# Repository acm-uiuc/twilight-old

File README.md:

# Twilight

## Usage

    pip install -r requirements.txt
    FLASK_APP=twilight.py flask run
    
## POSTing

    curl -H "token: foo" -X post http://localhost:5000 -d '{"abc":1}'

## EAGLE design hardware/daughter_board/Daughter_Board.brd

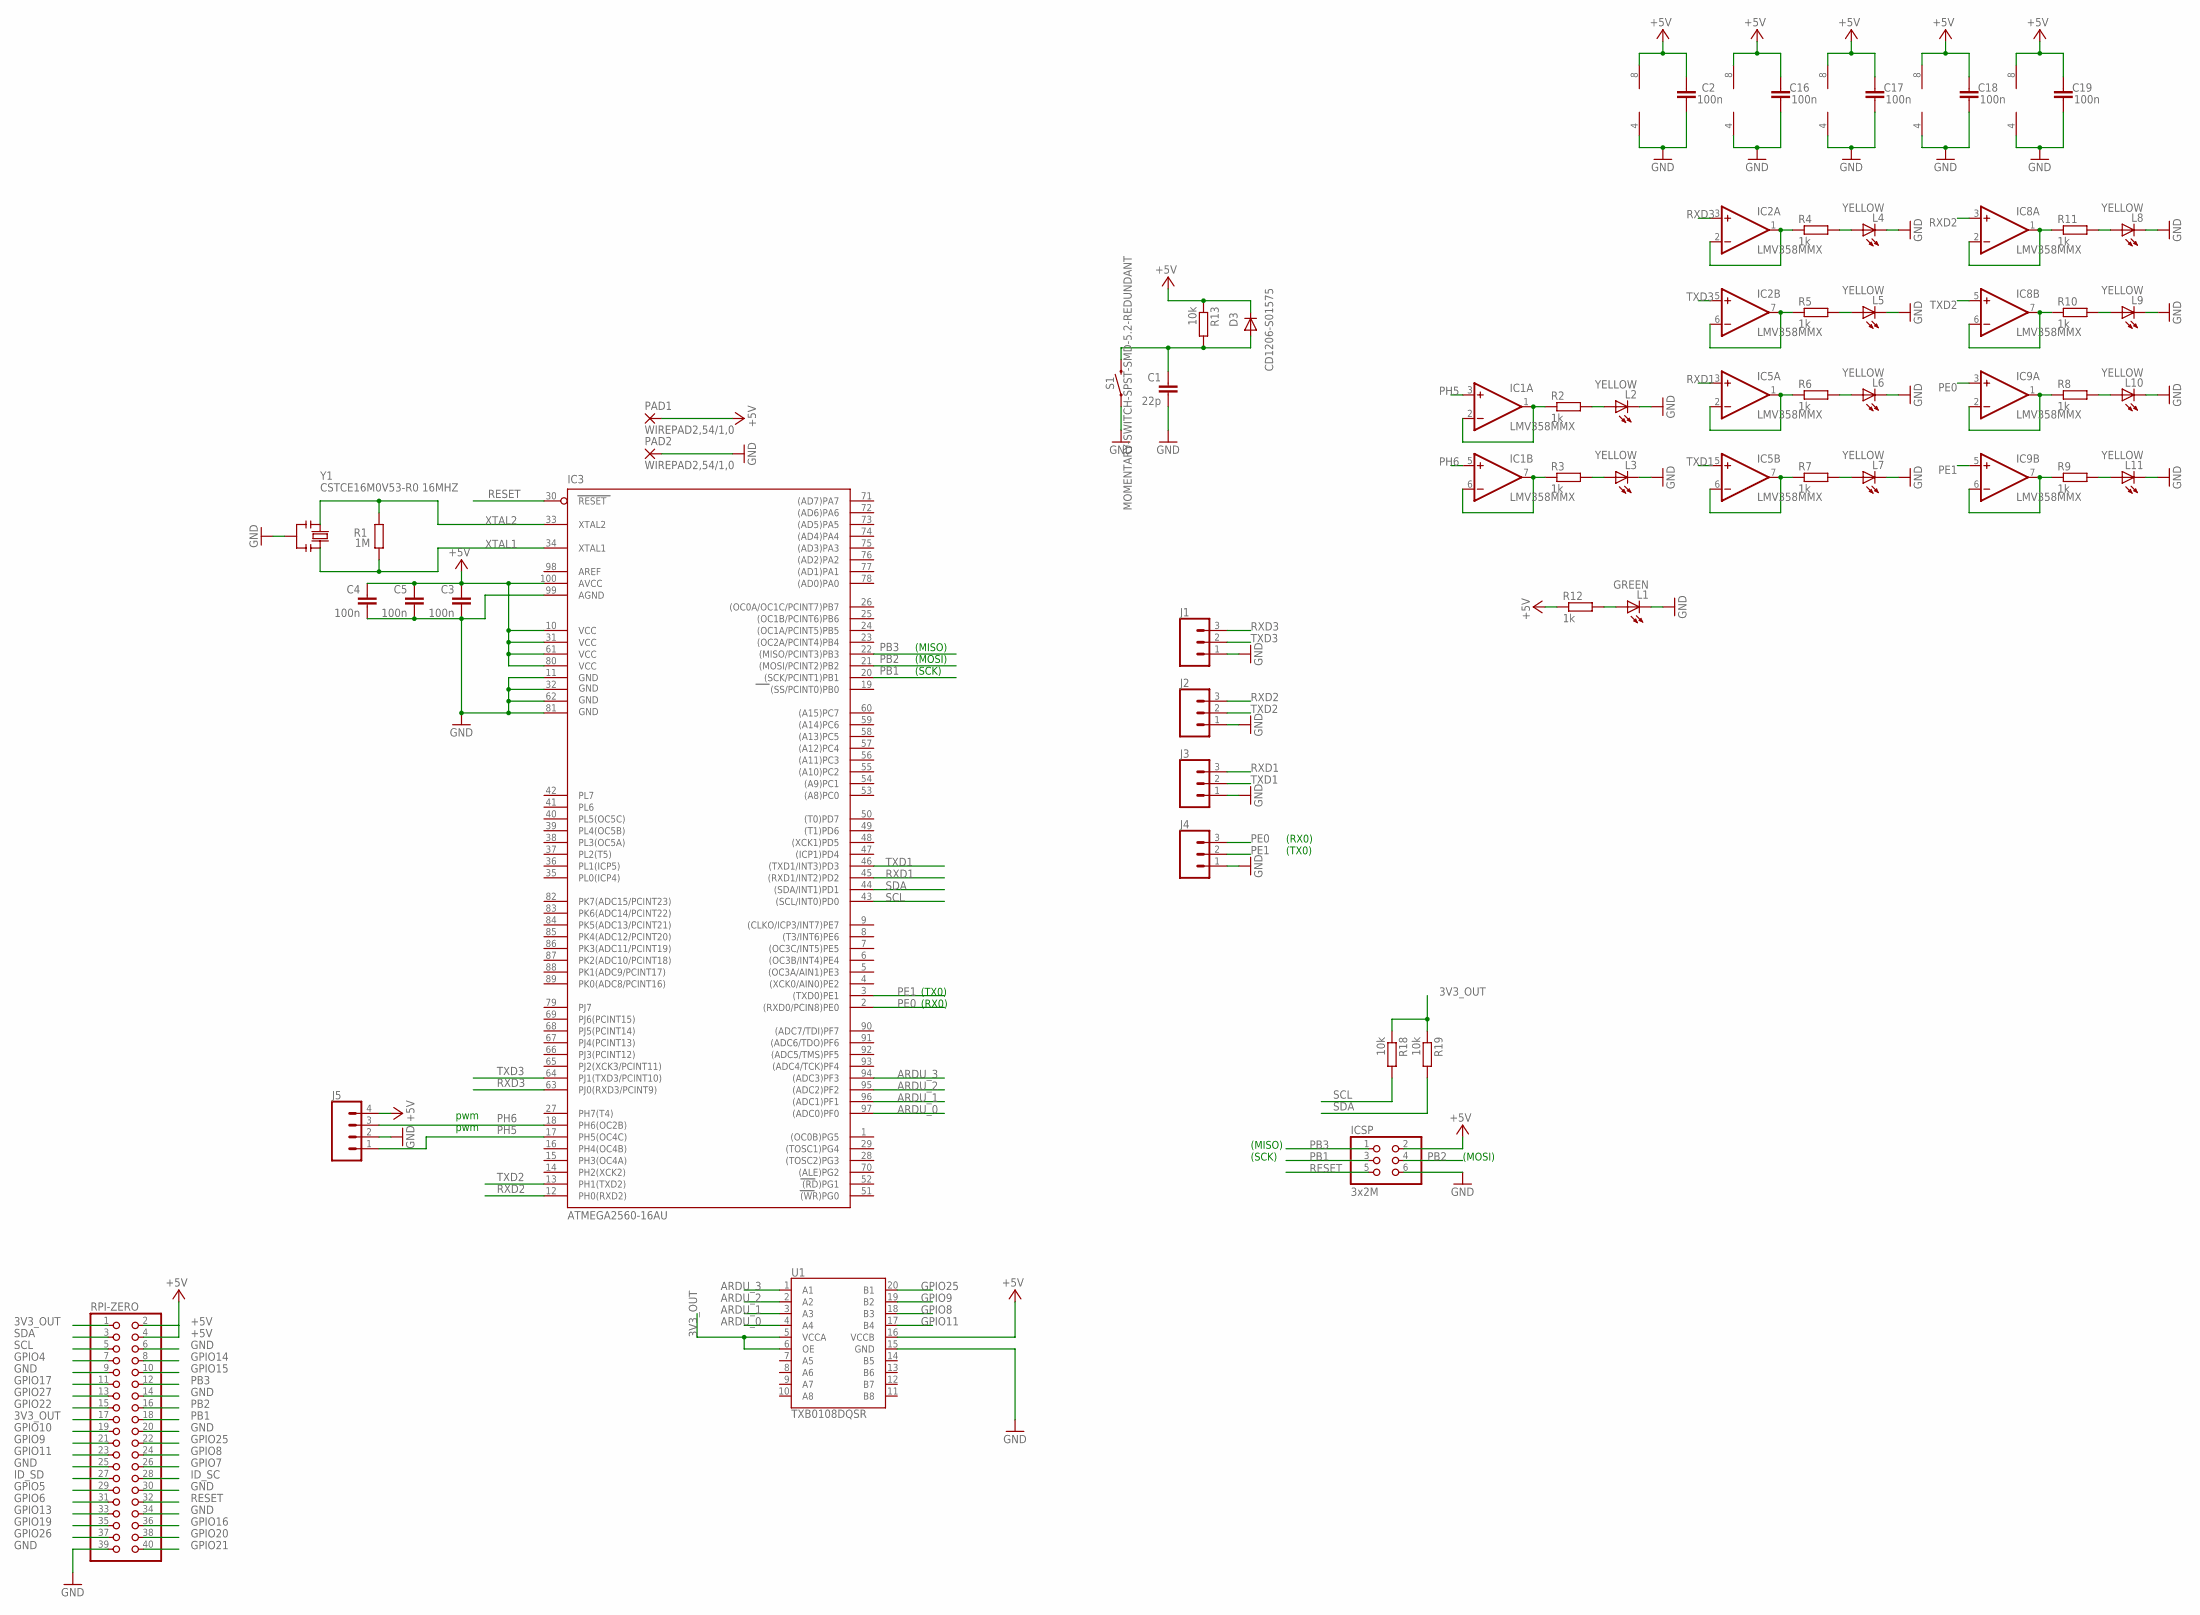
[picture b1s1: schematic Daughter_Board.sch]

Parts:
C1: 22p; C0603-ROUND
C2, C3, C4, C5, C16, C17, C18, C19: 100n; C0603-ROUND
D3: CD1206-S01575; MINIMELF
IC1, IC2, IC5, IC8, IC9: LMV358MMX; MSOP08
IC3: ATMEGA2560-16AU; TQFP100
ICSP: 3x2M; 2X03
J1, J2, J3, J4: CONN_03; 1X03
J5: CONN_04; 1X04
L1: GREEN; CHIP-LED0805
L2, L3, L4, L5, L6, L7, L8, L9, L10, L11: YELLOW; CHIP-LED0805
PAD1, PAD2: WIREPAD2,54/1,0; 2,54/1,0
R1: 1M; R0603-ROUND
R2, R3, R4, R5, R6, R7, R8, R9, R10, R11, R12: 1k; R0603
R13, R18, R19: 10k; R0603
RPI-ZERO: PINHD-2X20; 2X20
S1: MOMENTARY-SWITCH-SPST-SMD-5.2-REDUNDANT; TACTILE_SWITCH_SMD_5.2MM
U1: TXB0108DQSR; UFDFN-20
Y1: CSTCE16M0V53-R0 16MHZ; RESONATOR

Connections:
3V3_OUT: R18.1, R19.1, RPI-ZERO.1, RPI-ZERO.17, U1.5 (VCCA), U1.6 (OE)
+5V: C2.2, C3.1, C4.1, C5.1, C16.2, C17.2, C18.2, C19.2, D3.C, IC1.8 (V+), IC2.8 (V+), IC3.10 (VCC), IC3.31 (VCC1), IC3.61 (VCC2), IC3.80 (VCC3), IC3.100 (AVCC), IC5.8 (V+), IC8.8 (V+), IC9.8 (V+), ICSP.2, J5.4, PAD1.1, R12.1, R13.1, RPI-ZERO.2, RPI-ZERO.4, U1.16 (VCCB)
ARDU_0: IC3.97 ((ADC0)PF0), U1.4 (A4)
ARDU_1: IC3.96 ((ADC1)PF1), U1.3 (A3)
ARDU_2: IC3.95 ((ADC2)PF2), U1.2 (A2)
ARDU_3: IC3.94 ((ADC3)PF3), U1.1 (A1)
GND: C1.2, C2.1, C3.2, C4.2, C5.2, C16.1, C17.1, C18.1, C19.1, IC1.4 (V-), IC2.4 (V-), IC3.11 (GND), IC3.32 (GND1), IC3.62 (GND2), IC3.81 (GND3), IC3.99 (AGND), IC5.4 (V-), IC8.4 (V-), IC9.4 (V-), ICSP.6, J1.1, J2.1, J3.1, J4.1, J5.2, L1.C, L2.C, L3.C, L4.C, L5.C, L6.C, L7.C, L8.C, L9.C, L10.C, L11.C, PAD2.1, RPI-ZERO.6, RPI-ZERO.9, RPI-ZERO.14, RPI-ZERO.20, RPI-ZERO.25, RPI-ZERO.30, RPI-ZERO.34, RPI-ZERO.39, S1.1, S1.2 (1), U1.15 (GND), Y1.2
GPIO4: RPI-ZERO.7
GPIO5: RPI-ZERO.29
GPIO6: RPI-ZERO.31
GPIO7: RPI-ZERO.26
GPIO8: RPI-ZERO.24, U1.18 (B3)
GPIO9: RPI-ZERO.21, U1.19 (B2)
GPIO10: RPI-ZERO.19
GPIO11: RPI-ZERO.23, U1.17 (B4)
GPIO13: RPI-ZERO.33
GPIO14: RPI-ZERO.8
GPIO15: RPI-ZERO.10
GPIO16: RPI-ZERO.36
GPIO17: RPI-ZERO.11
GPIO19: RPI-ZERO.35
GPIO20: RPI-ZERO.38
GPIO21: RPI-ZERO.40
GPIO22: RPI-ZERO.15
GPIO25: RPI-ZERO.22, U1.20 (B1)
GPIO26: RPI-ZERO.37
GPIO27: RPI-ZERO.13
ID_SC: RPI-ZERO.28
ID_SD: RPI-ZERO.27
unnamed: L3.A, R3.2
unnamed: L2.A, R2.2
unnamed: L1.A, R12.2
unnamed: IC1.1 (OUT), IC1.2 (-IN), R2.1
unnamed: IC5.6 (-IN), IC5.7 (OUT), R7.1
unnamed: IC1.6 (-IN), IC1.7 (OUT), R3.1
unnamed: IC5.1 (OUT), IC5.2 (-IN), R6.1
unnamed: IC2.6 (-IN), IC2.7 (OUT), R5.1
unnamed: IC2.1 (OUT), IC2.2 (-IN), R4.1
unnamed: L4.A, R4.2
unnamed: L5.A, R5.2
unnamed: IC8.1 (OUT), IC8.2 (-IN), R11.1
unnamed: L7.A, R7.2
unnamed: L6.A, R6.2
unnamed: IC8.6 (-IN), IC8.7 (OUT), R10.1
unnamed: IC9.1 (OUT), IC9.2 (-IN), R8.1
unnamed: IC9.6 (-IN), IC9.7 (OUT), R9.1
unnamed: L11.A, R9.2
unnamed: L10.A, R8.2
unnamed: L8.A, R11.2
unnamed: L9.A, R10.2
PB1: IC3.20 ((SCK/PCINT1)PB1), ICSP.3, RPI-ZERO.18
PB2: IC3.21 ((MOSI/PCINT2)PB2), ICSP.4, RPI-ZERO.16
PB3: IC3.22 ((MISO/PCINT3)PB3), ICSP.1, RPI-ZERO.12
PE0: IC3.2 ((RXD0/PCIN8)PE0), IC9.3 (+IN), J4.3
PE1: IC3.3 ((TXD0)PE1), IC9.5 (+IN), J4.2
PH5: IC1.3 (+IN), IC3.17 (PH5(OC4C)), J5.1
PH6: IC1.5 (+IN), IC3.18 (PH6(OC2B)), J5.3
RESET: C1.1, D3.A, IC3.30 (RESET), ICSP.5, R13.2, RPI-ZERO.32, S1.3 (2), S1.4 (2)
RXD1: IC3.45 ((RXD1/INT2)PD2), IC5.3 (+IN), J3.3
RXD2: IC3.12 (PH0(RXD2)), IC8.3 (+IN), J2.3
RXD3: IC2.3 (+IN), IC3.63 (PJ0(RXD3/PCINT9)), J1.3
SCL: IC3.43 ((SCL/INT0)PD0), R18.2, RPI-ZERO.5
SDA: IC3.44 ((SDA/INT1)PD1), R19.2, RPI-ZERO.3
TXD1: IC3.46 ((TXD1/INT3)PD3), IC5.5 (+IN), J3.2
TXD2: IC3.13 (PH1(TXD2)), IC8.5 (+IN), J2.2
TXD3: IC2.5 (+IN), IC3.64 (PJ1(TXD3/PCINT10)), J1.2
XTAL1: IC3.34 (XTAL1), R1.1, Y1.3
XTAL2: IC3.33 (XTAL2), R1.2, Y1.1

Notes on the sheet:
pwm
(TX0)
(RX0)
(MISO)
(SCK)
(MOSI)

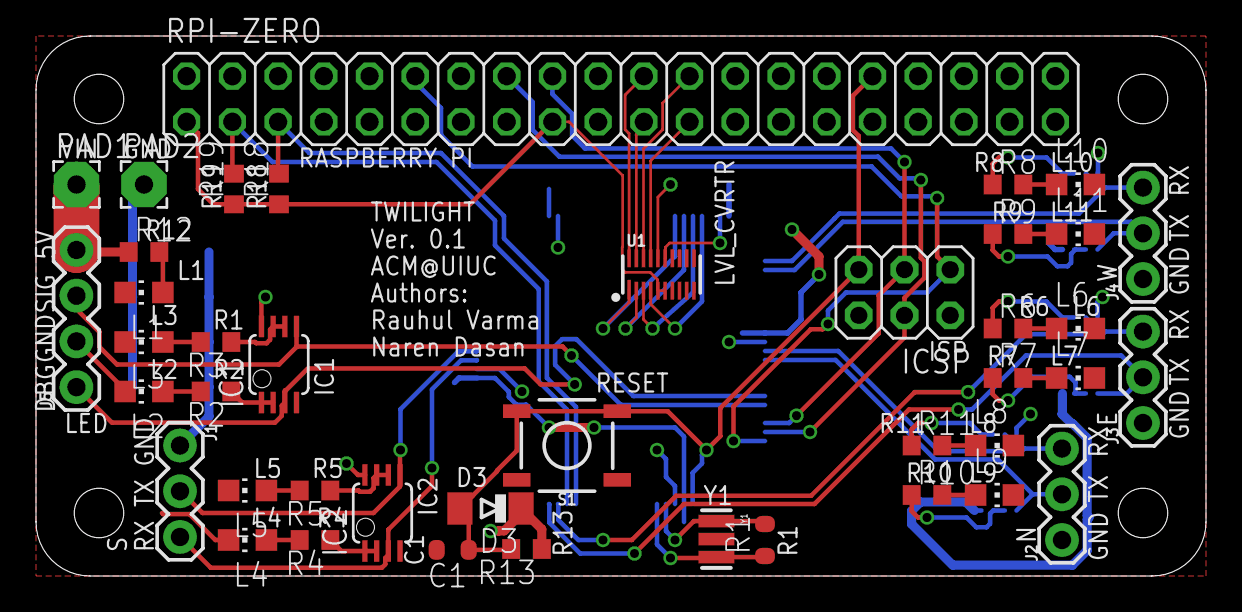
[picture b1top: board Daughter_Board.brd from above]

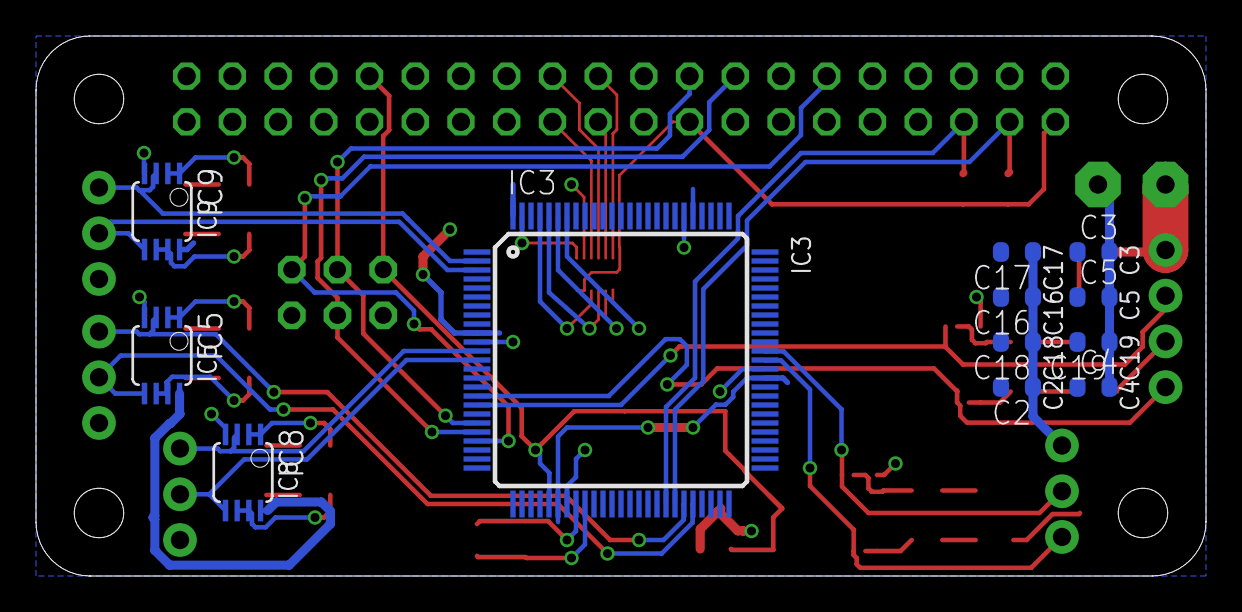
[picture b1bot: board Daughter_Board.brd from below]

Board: 2 copper layers, 65.0 x 30.0 mm, 54 parts (12 on the bottom side), 50 nets.

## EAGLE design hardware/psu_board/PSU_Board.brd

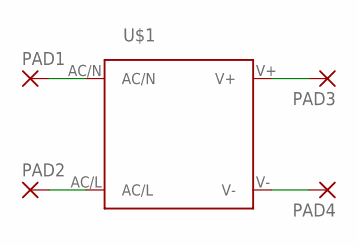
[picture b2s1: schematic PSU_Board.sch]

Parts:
PAD1, PAD2, PAD3, PAD4: 3,81/1,4
U$1: IRM_15/20

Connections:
AC_L_IN: PAD2.1, U$1.AC/L
AC_N_IN: PAD1.1, U$1.AC/N
DC_HIGH_OUT: PAD3.1, U$1.V+
DC_LOW_OUT: PAD4.1, U$1.V-

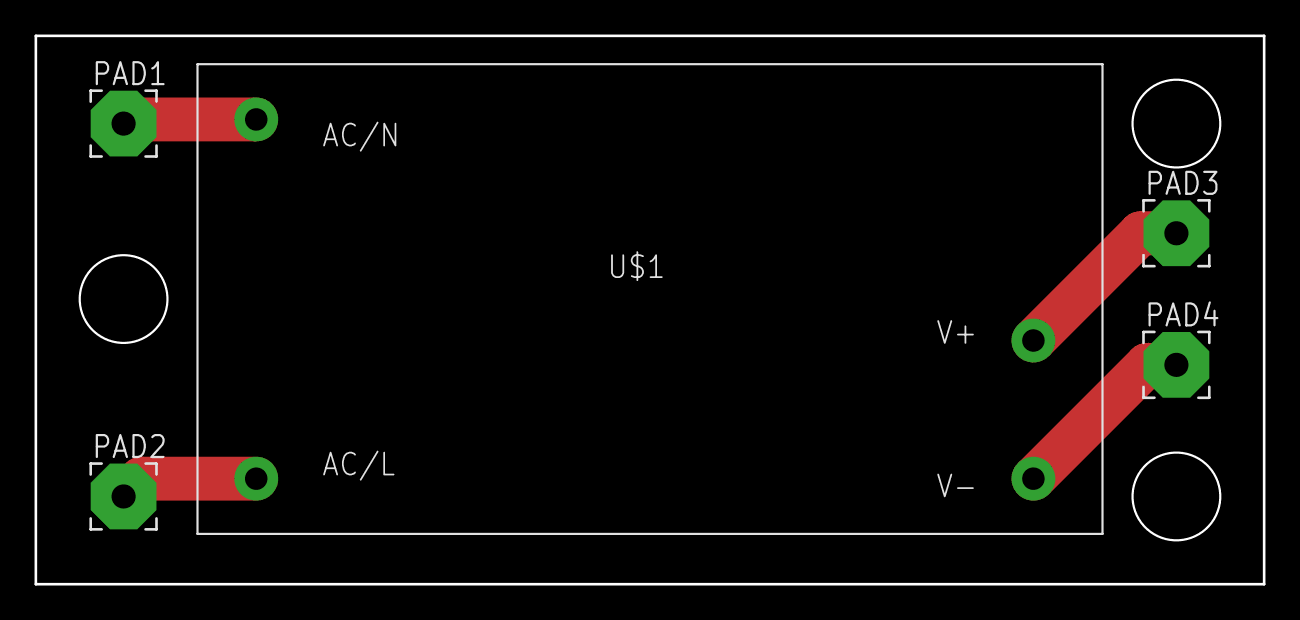
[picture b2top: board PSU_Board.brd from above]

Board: 2 copper layers, 71.1 x 31.8 mm, 5 parts (0 on the bottom side), 4 nets.

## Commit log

2017-03-10 Initial commit with bad code
2017-03-10 Add Arduino controller code
2017-03-11 Creating API
2017-03-11 added gitignore
2017-03-11 added ipynb to gitignore
2017-03-11 Build more of the API. Mood_lights is now using the api.
2017-03-11 changes after testing in prod
2017-03-11 removed annyoing debug line
2017-03-11 fixed configs
2017-03-11 fixed rgb/rbg issue
2017-03-11 Created README.
2017-03-11 Added clamp
2017-03-11 Fixed documentation for clamp
2017-03-12 Added rate limiting.
2017-03-12 moved blocking state setter out of object
2017-03-12 Add code to check how many LEDs are in a panel
2017-03-12 random light colors
2017-03-12 spelling
2017-03-13 Added terrible animation
2017-03-13 Module now clamps values to [0,254]. Simplified mood_lights
2017-03-14 Write to serial ports in separate threads; update requirements.txt
2017-03-14 Set up Travis CI to run flake8
2017-03-14 creating dynamic config reloader
2017-03-14 silly config updater
2017-03-15 Enforce default values for config variables, move methods into interface class
2017-03-15 Add serial port enumeration code
2017-03-15 FEATURE #2: Plugin manager
2017-03-15 Extend communication protocol, remove CLAMP parameter
2017-03-15 fixed import and extra line
2017-03-15 Make plugins subclass from base class
2017-03-15 Fix some issues with plugin manager
2017-03-15 Use plugin.ready() when displaying frames, add docstrings
2017-03-16 Made requested changes
2017-03-16 Add FPS counter, increase default baud rate on Arduino
2017-03-16 Change defaults
2017-03-16 Add docstrings
2017-03-16 Optimize EEPROM write function, add EEPROM read, add documentation
2017-03-16 Change LED driver pin, fix some compilation issues
2017-03-23 Add fading and scrolling
2017-03-23 Port spectrum analyzer to Twilight plugin
2017-03-23 Use system audio output for spectrum analysis
2017-03-25 FEATURE #14: Apply filters to light data frames
2017-03-25 fixed issues from change requests
2017-03-25 Fix some bugs
2017-03-25 edited to match PEP8 standards
2017-03-28 added plugin and filter parameters
2017-03-28 move playing plugins to separate thread
2017-03-29 Add Raspberry Pi disk image preparation script
2017-03-29 Start work on client-server
2017-04-03 Add Gitter badge
2017-10-17 clean out the repo
2017-10-17 multinode serial test
2017-10-24 pi side boilerplate
2017-10-24 control structure
2017-10-31 initial PIC simulator
2017-11-01 Initial revisions for both the daughter baord and psu board
2017-11-01 partial implementation of daughter board with rpi as bootloader
2017-11-02 backup
2017-11-02 route icsp header
2017-11-02 level converter and labels
2017-11-02 forgot a label
2017-11-02 fix issues generated by seeedstudio dru
2017-11-04 some DRC fixes
2017-11-04 export gerber files and create bom
2017-11-04 Daughter Board v1
2017-11-04 update silkscreen and export gerber files
2017-11-06 clean up schematic, add board images
2017-11-07 localization msgs
2017-11-07 developing the message bus
2017-11-10 setup scripts
2017-11-10 blink build
2017-11-10 new blink
2017-11-11 flash util
2017-11-11 most tests
2017-11-11 strand testing
2017-11-11 initial firmware source
2017-11-11 localization protocol
2017-11-11 pic device code
2017-11-11 toolchain
2017-11-11 new firmware
2017-11-12 initial control panel app structure
2017-11-12 build out app skeleton
2017-11-12 skeleton System Status view
2017-11-12 networking firmware
2017-11-12 debugging firmware
2017-11-12 firmware
2017-11-12 only embedded code now
2017-11-12 making this repo a manifest repo
2017-11-13 Update README.md
    merch -> twilight
2018-10-16 skeleton flask app
2019-02-02 add example code for uno

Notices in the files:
parts and their libraries:
SparkFun-Connectors: Licensing: Creative Commons ShareAlike 4.0 International - https://creativecommons.org/licenses/by-sa/4.0
